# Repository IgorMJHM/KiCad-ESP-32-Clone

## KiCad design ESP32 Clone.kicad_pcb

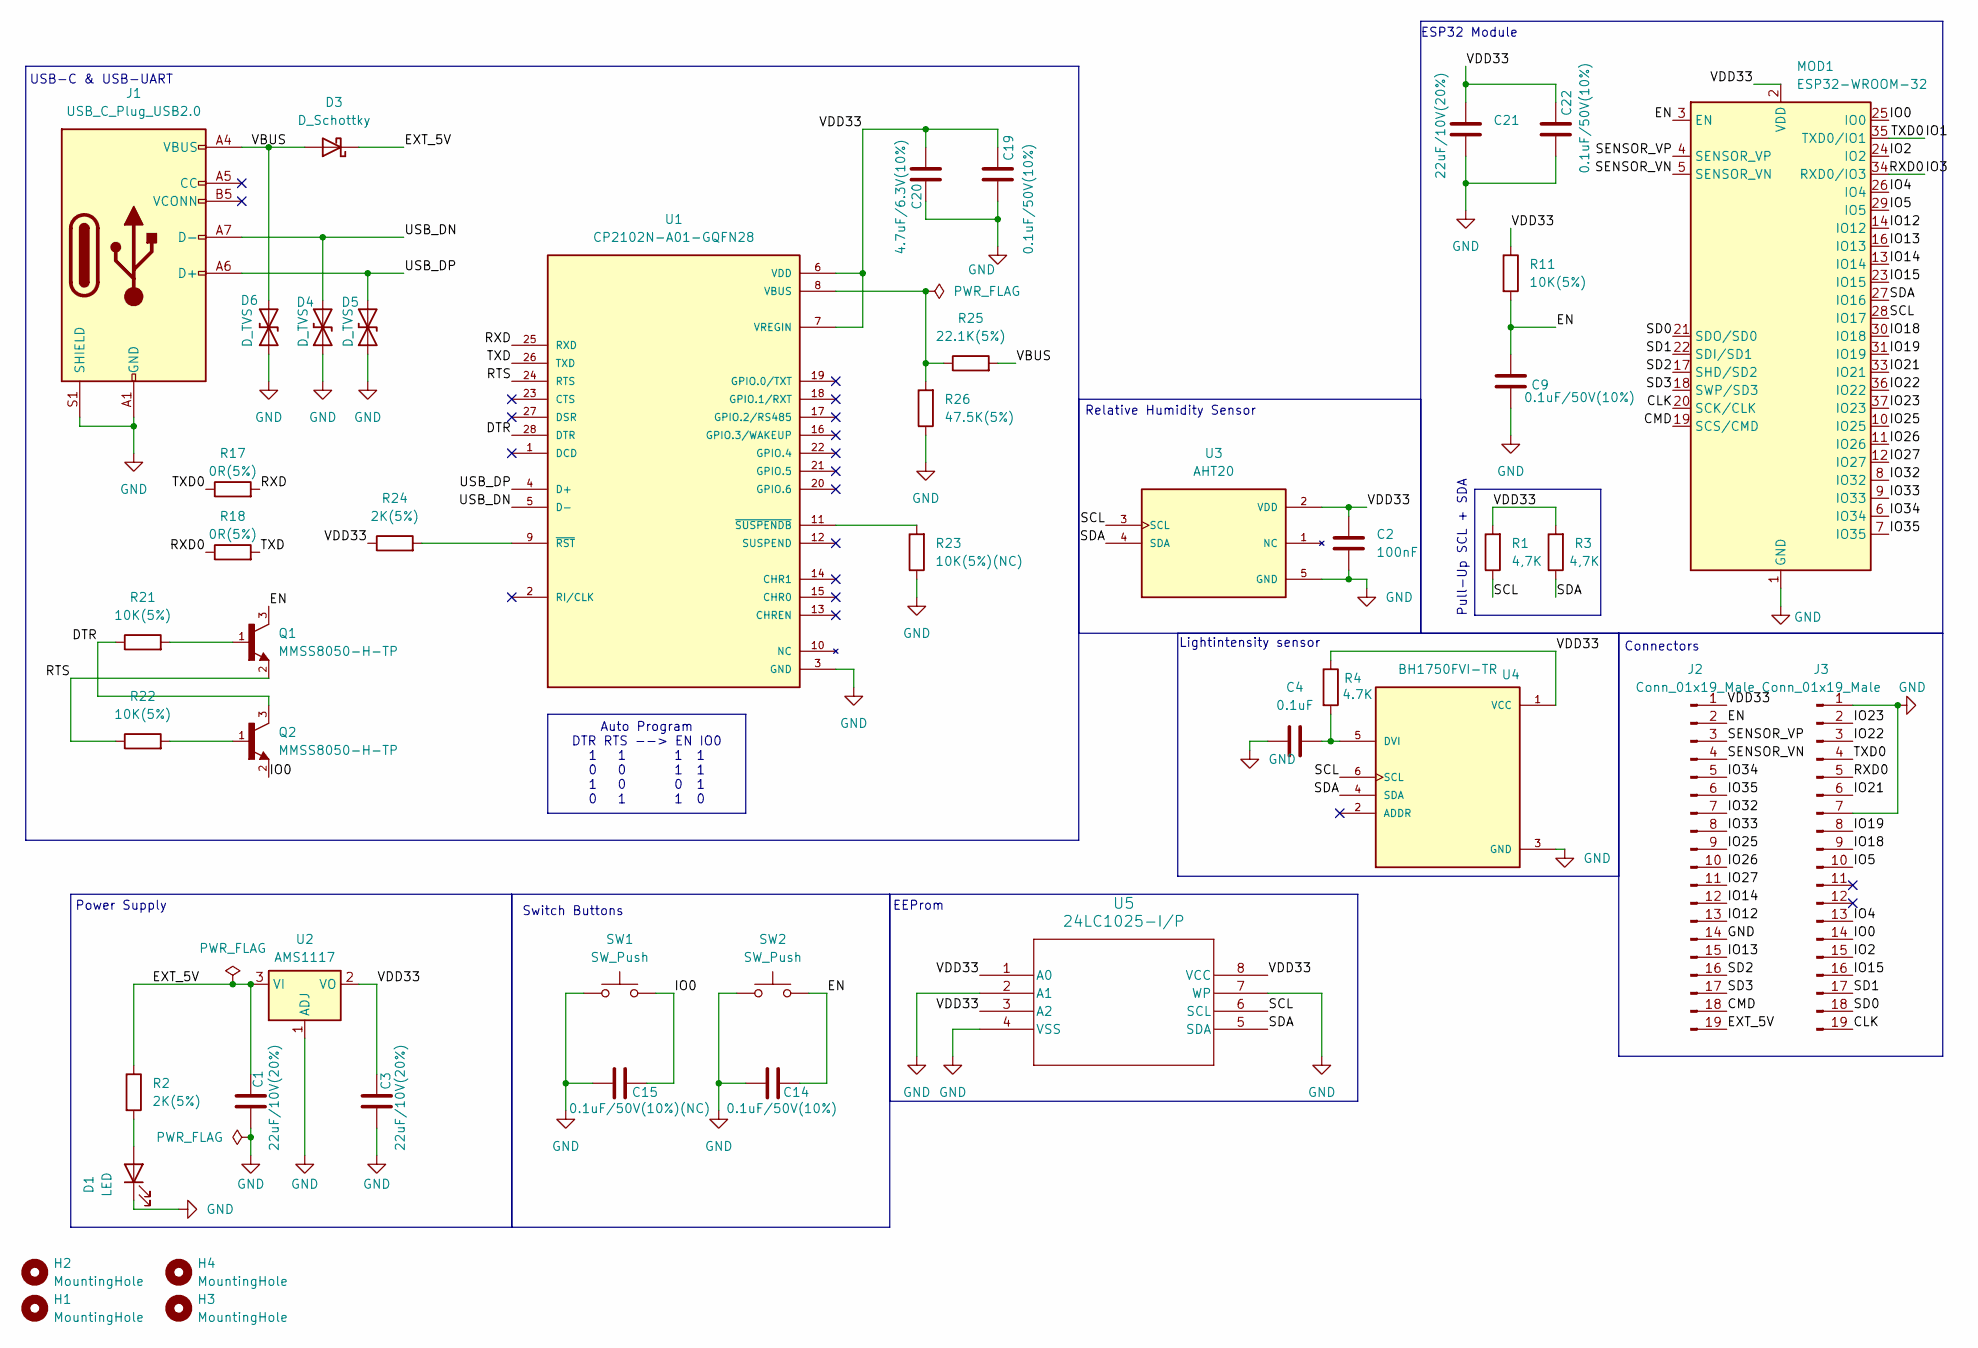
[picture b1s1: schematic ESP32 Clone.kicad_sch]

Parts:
C1, C3, C21: 22uF/10V(20%); C_0603_1608Metric
C2: 100nF; C_0402_1005Metric
C4: 0.1uF; C_0402_1005Metric
C9, C14, C19, C22: 0.1uF/50V(10%); C_0402_1005Metric
C15: 0.1uF/50V(10%)(NC); C_0402_1005Metric
C20: 4.7uF/6.3V(10%); C_0402_1005Metric
D1: LED; LED_0603_1608Metric
D3: D_Schottky; D_SOD-323
D4, D5, D6: D_TVS; D_SOD-323
H1, H2, H3, H4: MountingHole; MountingHole_2.1mm
J1: USB_C_Plug_USB2.0; USB_C_Plug_Molex_105444
J2, J3: Conn_01x19_Male; PinHeader_1x19_P2.54mm_Vertical
MOD1: ESP32-WROOM-32
Q1, Q2: MMSS8050-H-TP; TRANS_MMSS8050-H-TP; PARTREV D
R1, R3: 4,7K; R_0402_1005Metric
R2, R24: 2K(5%); R_0402_1005Metric
R4: 4.7K; R_0402_1005Metric
R11, R21, R22: 10K(5%); R_0402_1005Metric
R17, R18: 0R(5%); R_0402_1005Metric
R23: 10K(5%)(NC); R_0402_1005Metric
R25: 22.1K(5%); R_0402_1005Metric
R26: 47.5K(5%); R_0402_1005Metric
SW1, SW2: SW_Push; SW_SPST_B3S-1000
U1: CP2102N-A01-GQFN28; QFN50P500X500X80-29N; PARTREV 1.0
U2: AMS1117; SOT-223-3_TabPin2
U3: AHT20; PSON100P300X300X110-6N; PARTREV V1.0
U4: BH1750FVI-TR; XDCR_BH1750FVI-TR; PARTREV D
U5: 24LC1025-I/P; PDIP8_300MC_MCH

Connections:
/CLK: J3.19, MOD1.20 (SCK/CLK)
/CMD: J2.18, MOD1.19 (SCS/CMD)
/DTR: Q2.3, R21.1, U1.28 (DTR)
/EN: C9.1, C14.2, J2.2, MOD1.3 (EN), Q1.3, R11.2, SW2.2
/EXT_5V: C1.1, D3.1 (K), J2.19, R2.1, U2.3 (VI)
/IO0: C15.1, J3.14, MOD1.25 (IO0), Q2.2, SW1.2
/IO1: J3.4, MOD1.35 (TXD0/IO1), R17.1
/IO2: J3.15, MOD1.24 (IO2)
/IO3: J3.5, MOD1.34 (RXD0/IO3), R18.1
/IO4: J3.13, MOD1.26 (IO4)
/IO5: J3.10, MOD1.29 (IO5)
/IO12: J2.13, MOD1.14 (IO12)
/IO13: J2.15, MOD1.16 (IO13)
/IO14: J2.12, MOD1.13 (IO14)
/IO15: J3.16, MOD1.23 (IO15)
/IO18: J3.9, MOD1.30 (IO18)
/IO19: J3.8, MOD1.31 (IO19)
/IO21: J3.6, MOD1.33 (IO21)
/IO22: J3.3, MOD1.36 (IO22)
/IO23: J3.2, MOD1.37 (IO23)
/IO25: J2.9, MOD1.10 (IO25)
/IO26: J2.10, MOD1.11 (IO26)
/IO27: J2.11, MOD1.12 (IO27)
/IO32: J2.7, MOD1.8 (IO32)
/IO33: J2.8, MOD1.9 (IO33)
/IO34: J2.5, MOD1.6 (IO34)
/IO35: J2.6, MOD1.7 (IO35)
/RTS: Q1.2, R22.1, U1.24 (RTS)
/RXD: R17.2, U1.25 (RXD)
/SCL: MOD1.28 (IO17), R1.1, U3.3 (SCL), U4.6 (SCL), U5.6 (SCL)
/SD0: J3.18, MOD1.21 (SDO/SD0)
/SD1: J3.17, MOD1.22 (SDI/SD1)
/SD2: J2.16, MOD1.17 (SHD/SD2)
/SD3: J2.17, MOD1.18 (SWP/SD3)
/SDA: MOD1.27 (IO16), R3.1, U3.4 (SDA), U4.4 (SDA), U5.5 (SDA)
/SENSOR_VN: J2.4, MOD1.5 (SENSOR_VN)
/SENSOR_VP: J2.3, MOD1.4 (SENSOR_VP)
/TXD: R18.2, U1.26 (TXD)
/USB_DN: D4.2 (A2), J1.A7 (D-), U1.5 (D-)
/USB_DP: D5.2 (A2), J1.A6 (D+), U1.4 (D+)
/VBUS: D3.2 (A), D6.2 (A2), J1.A4 (VBUS), J1.A9 (VBUS), J1.B4 (VBUS), J1.B9 (VBUS), R25.2
/VDD33: C2.1, C3.1, C19.1, C20.1, C21.1, C22.1, J2.1, MOD1.2 (VDD), R1.2, R3.2, R4.1, R11.1, R24.1, U1.6 (VDD), U1.7 (VREGIN), U2.2 (VO), U3.2 (VDD), U4.1 (VCC), U5.1 (A0), U5.3 (A2), U5.8 (VCC)
GND: C1.2, C2.2, C3.2, C4.1, C9.2, C14.1, C15.2, C19.2, C20.2, C21.2, C22.2, D1.1 (K), D4.1 (A1), D5.1 (A1), D6.1 (A1), J1.A1 (GND), J1.A12 (GND), J1.B1 (GND), J1.B12 (GND), J1.S1 (SHIELD), J2.14, J3.1, J3.7, MOD1.1 (GND), MOD1.15 (GND), MOD1.38 (GND), MOD1.39 (GND), R23.1, R26.1, SW1.1, SW2.1, U1.3 (GND), U1.29 (GND), U2.1 (ADJ), U3.5 (GND), U4.3 (GND), U5.2 (A1), U5.4 (VSS), U5.7 (WP)
unnamed: D1.2 (A), R2.2
unnamed: Q1.1, R21.2
unnamed: Q2.1, R22.2
unnamed: R25.1, R26.2, U1.8 (VBUS)
unnamed: R24.2, U1.9 (~RST)
unnamed: R23.2, U1.11 (~SUSPENDB)
unnamed: C4.2, R4.2, U4.5 (DVI)

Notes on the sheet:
Power Supply
Connectors
Switch Buttons
EEProm
Relative Humidity Sensor
Pull-Up SCL + SDA
USB-C & USB-UART
ESP32 Module
Lightintensity sensor
Auto Program DTR RTS --> EN IO0 1 1 1 1 0 0 1 1 1 0 0 1 0 1 1 0

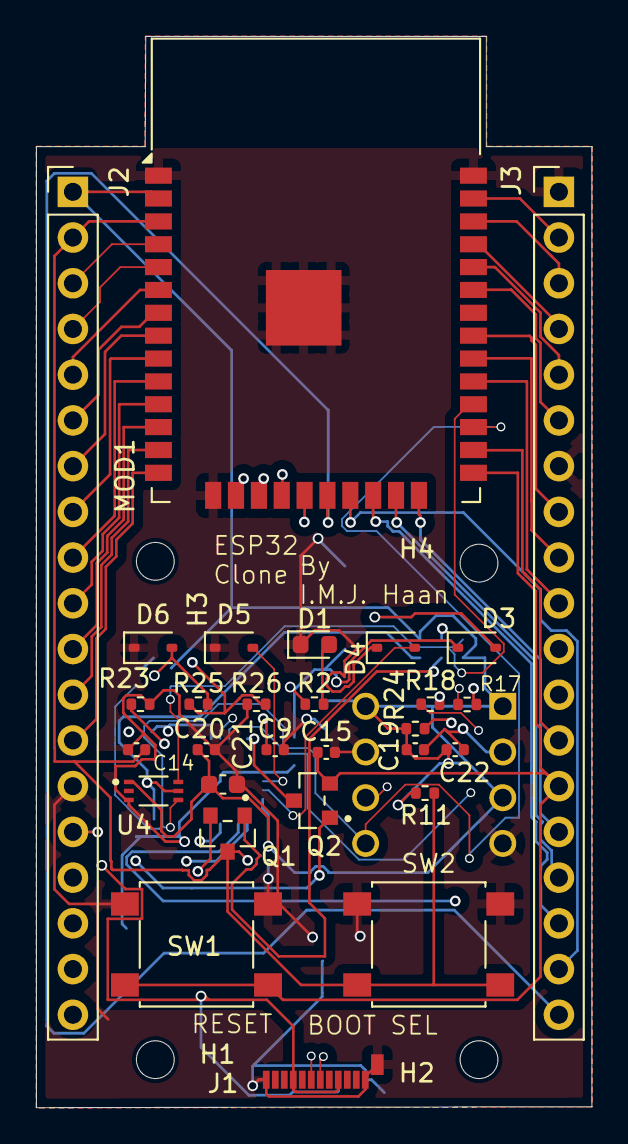
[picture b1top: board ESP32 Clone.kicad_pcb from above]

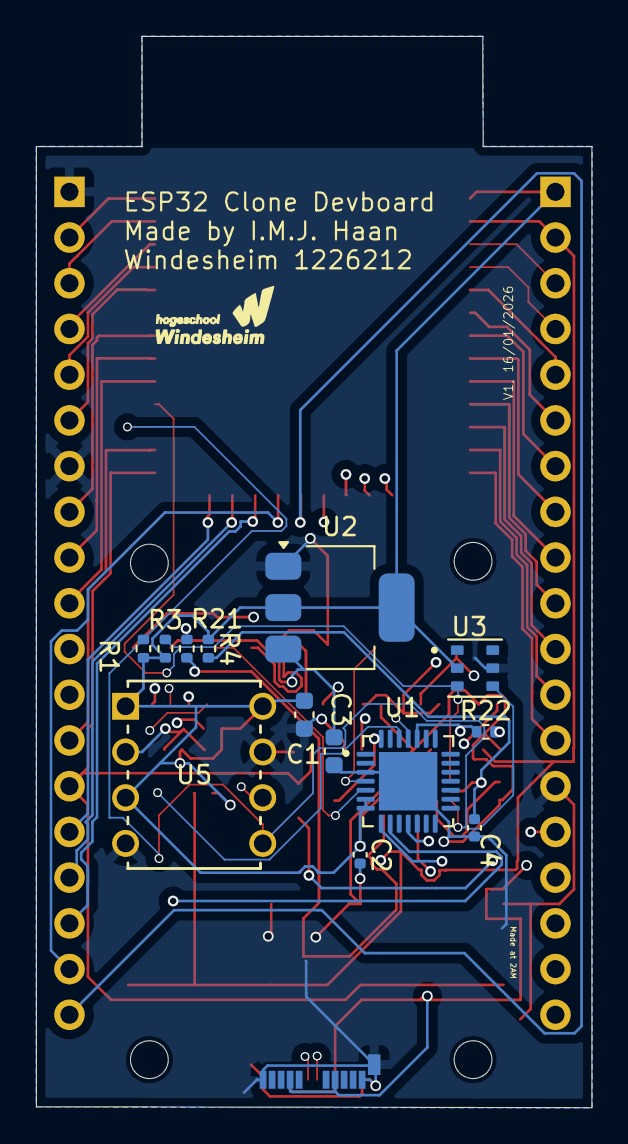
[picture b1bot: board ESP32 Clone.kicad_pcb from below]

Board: 4 copper layers, 30.9 x 59.5 mm, 46 parts (13 on the bottom side), 50 nets.

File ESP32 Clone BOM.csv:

"Reference","Qty","Value","DNP","Exclude from BOM","Exclude from Board","Footprint","Datasheet"
"C1,C3,C21","3","22uF/10V(20%)","","","","Capacitor_SMD:C_0603_1608Metric","~"
"C2","1","100nF","","","","Capacitor_SMD:C_0402_1005Metric","~"
"C4","1","0.1uF","","","","Capacitor_SMD:C_0402_1005Metric","~"
"C9,C14,C19,C22","4","0.1uF/50V(10%)","","","","Capacitor_SMD:C_0402_1005Metric","~"
"C15","1","0.1uF/50V(10%)(NC)","","","","Capacitor_SMD:C_0402_1005Metric","~"
"C20","1","4.7uF/6.3V(10%)","","","","Capacitor_SMD:C_0402_1005Metric","~"
"D1","1","LED","","","","LED_SMD:LED_0603_1608Metric","~"
"D3","1","D_Schottky","","","","Diode_SMD:D_SOD-323","~"
"D4,D5,D6","3","D_TVS","","","","Diode_SMD:D_SOD-323","~"
"H1,H2,H3,H4","4","MountingHole","","Excluded from BOM","","MountingHole:MountingHole_2.1mm","~"
"J1","1","USB_C_Plug_USB2.0","","","","Connector_USB:USB_C_Plug_Molex_105444","https://www.usb.org/sites/default/files/documents/usb_type-c.zip"
"J2,J3","2","Conn_01x19_Male","","","","Connector_PinHeader_2.54mm:PinHeader_1x19_P2.54mm_Vertical","~"
"MOD1","1","ESP32-WROOM-32","","","","RF_Module:ESP32-WROOM-32","https://www.espressif.com/sites/default/files/documentation/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"
"Q1,Q2","2","MMSS8050-H-TP","","","","MMSS8050-H-TP:TRANS_MMSS8050-H-TP",""
"R1,R3","2","4,7K","","","","Resistor_SMD:R_0402_1005Metric","~"
"R2,R24","2","2K(5%)","","","","Resistor_SMD:R_0402_1005Metric","~"
"R4","1","4.7K","","","","Resistor_SMD:R_0402_1005Metric","~"
"R11,R21,R22","3","10K(5%)","","","","Resistor_SMD:R_0402_1005Metric","~"
"R17,R18","2","0R(5%)","","","","Resistor_SMD:R_0402_1005Metric","~"
"R23","1","10K(5%)(NC)","","","","Resistor_SMD:R_0402_1005Metric","~"
"R25","1","22.1K(5%)","","","","Resistor_SMD:R_0402_1005Metric","~"
"R26","1","47.5K(5%)","","","","Resistor_SMD:R_0402_1005Metric","~"
"SW1,SW2","2","SW_Push","","","","Button_Switch_SMD:SW_SPST_B3S-1000","~"
"U1","1","CP2102N-A01-GQFN28","","","","CP2102N-A01-GQFN28:QFN50P500X500X80-29N",""
"U2","1","AMS1117","","","","Package_TO_SOT_SMD:SOT-223-3_TabPin2","http://www.advanced-monolithic.com/pdf/ds1117.pdf"
"U3","1","AHT20","","","","AHT20:PSON100P300X300X110-6N",""
"U4","1","BH1750FVI-TR","","","","BH1750FVI-TR:XDCR_BH1750FVI-TR",""
"U5","1","24LC1025-I/P","","","","PDIP8_300MC_MCH","24LC1025-I/P"

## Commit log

2026-01-13 Initial KiCad project
2026-01-13 Paar Net labels en draden gemaakt
2026-01-16 SCHEMA KLAAR
